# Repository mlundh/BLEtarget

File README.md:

# BLEtarget 
BLEtarget is an optical electronic scoring target with bluetooth connectivity developed for air guns. 

The project consists of both Hardware and firmware. The source is found in hw and fw respectively. 

## HW
The HW is developed in KiCad 7.0. It consists of a sensor array with support electronics as well as an STM32 with BLE capabilites. 

### Known bugs
BOM error - U8-U10 MCP604 populated with MCP6044 with 14kHz bandwidth, should be MCP604 with 2.8Mhz bandwidth.
BOM error - c32 and corresponding 10u caps should be changed to 10000PF for a shorter signal pulse.
Schematic error - add a jumper to select master/slave. 
Schematic update - add a small memory, fram.

## FW
The firmware developed in CubeIDE.

## SW
The user interface is called Bullseye and developed in Qt using widgets.

### Dependencies
qt6-base-dev-tools
qt6-serialport-dev
cmake

### Raspberry pi Zero 2W with Hyperpixel 4.0 Square
#### Increase swap file:
Edit /etc/dphys-swapfile to change CONF_SWAPSIZE=100 to CONF_SWAPSIZE=2048. After making the change, restart the Pi.
#### Enable Hyperpixel
Add one line in /boot/firmware/config.txt:
dtoverlay=vc4-kms-dpi-hyperpixel4sq
#### Convenience
Enable one-click open of files: 
In Accessories select File Manager
In File Manage select Preference.
Select "Open Files with One Click"
#### Add desktop shortcut
Add desktop shortcut by draging the application to the desktop. Also drag the updateBullseye.sh script to the desktop.

#### Start at bootup

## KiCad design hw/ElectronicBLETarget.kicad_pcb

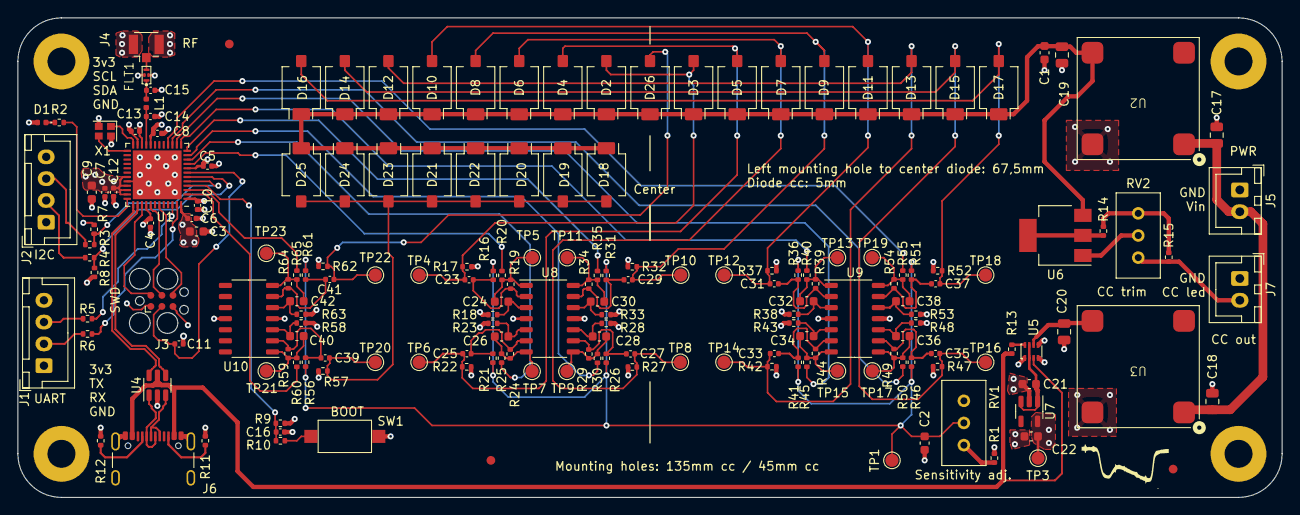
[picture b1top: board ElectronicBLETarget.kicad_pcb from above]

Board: 4 copper layers, 145.0 x 55.0 mm, 185 parts (0 on the bottom side), 91 nets.

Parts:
C1, C2, C3, C9, C21, C22: 4u7; C_0603_1608Metric
C4, C5, C6, C7, C8, C10, C11, C12, C13, C16, C23, C25, C27, C29, C31, C33, C35, C37, C39, C41: 100n; C_0402_1005Metric
C14: 0p8; C_0402_1005Metric
C15: 0p3; C_0402_1005Metric
C17, C18: 10u; C_0805_2012Metric
C19, C20: 22u; C_0805_2012Metric
C24, C26, C28, C30, C32, C34, C36, C38, C40, C42: 10u; C_0603_1608Metric
D1: LED; LED_0402_1005Metric
D2, D3, D4, D5, D6, D7, D8, D9, D10, D11, D12, D13, D14, D15, D16, D17, D18, D19, D20, D21, D22, D23, D24, D25, D26: BPW34-SMD; Osram_BPW34S-SMD
FLT1: DLF162500LT-5028A1
FM1, FM2, FM3: Fiducial; Fiducial_1mm_Mask2mm
H1, H2, H3, H4: MountingHole_Pad; MountingHole_3.2mm_M3_Pad
J1, J2: Conn_01x04; JST_XH_B4B-XH-A_1x04_P2.50mm_Vertical
J3: Conn_ARM_SWD_TagConnect_TC2030; Tag-Connect_TC2030-IDC-FP_2x03_P1.27mm_Vertical
J4: Conn_Coaxial; U.FL_Hirose_U.FL-R-SMT-1_Vertical
J5, J7: Conn_01x02; JST_XH_B2B-XH-A_1x02_P2.50mm_Vertical
J6: USB_C_Receptacle_USB2.0; USB_C_Receptacle_GCT_USB4105-xx-A_16P_TopMnt_Horizontal
L1: 2n7; L_0402_1005Metric
R1: 20k; R_0402_1005Metric
R2, R3, R4, R5, R6, R10, R20, R25, R30, R35, R40, R45, R50, R55, R60, R65: 220R; R_0402_1005Metric
R7, R8, R13, R17, R22, R27, R32, R37, R42, R47, R52, R57, R62: 5.6k; R_0402_1005Metric
R9, R11, R12: 5k1; R_0402_1005Metric
R14: 10R; R_0402_1005Metric
R15: 22R; R_0402_1005Metric
R16, R21, R26, R31, R36, R41, R46, R51, R56, R61: 100K; R_0402_1005Metric
R18, R23, R28, R33, R38, R43, R48, R53, R58, R63: 150K; R_0402_1005Metric
R19, R24, R29, R34, R39, R44, R49, R54, R59, R64: 1M; R_0402_1005Metric
RV1, RV2: 3296W; Potentiometer_Bourns_3296W_Vertical
SW1: SW_Push; SW_SPST_CK_RS282G05A3
TP1, TP3, TP4, TP5, TP6, TP7, TP8, TP9, TP10, TP11, TP12, TP13, TP14, TP15, TP16, TP17, TP18, TP19, TP20, TP21, TP22, TP23: TestPoint; TestPoint_Pad_D1.5mm
U1: STM32WB55CEU6; QFN-48-1EP_7x7mm_P0.5mm_EP5.6x5.6mm
U2: PXO7809-500-M-TR; PXO7805-500-M-TR
U3: PXO7805-500-M-TR
U4: USBLC6-2SC6; SOT-23-6
U5: LM66200; SOT-583-8
U6: LM317_SOT-223; SOT-223-3_TabPin2
U7: MIC5365-3.3YD5; SOT-23-5
U8, U9, U10: MCP604; SOIC-14_3.9x8.7mm_P1.27mm
X1: 32MHz, NX2016SA-32M; Crystal_SMD_2016-4Pin_2.0x1.6mm

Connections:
+3V3: C3.1, C4.1, C5.1, C6.1, C7.1, C8.1, C9.1, C10.1, C12.1, C13.1, C22.1, D1.2 (A), J1.4, J2.4, J3.1 (VCC), R1.1, R7.1, R8.1, SW1.2, TP3.1, U1.1 (VBAT), U1.8 (VDDA), U1.20 (VDD), U1.23 (VDDRF), U1.31 (VFBSMPS), U1.33 (VLXSMPS), U1.34 (VDDSMPS), U1.35 (VDD), U1.40 (VDDUSB), U1.48 (VDD), U7.5 (VOUT), U8.4 (V+), U9.4 (V+), U10.4 (V+)
+5V: C21.1, U5.2 (VOUT), U5.7 (VOUT), U7.1 (VIN), U7.3 (EN)
+9V: C1.1, C19.1, D2.1 (K), D3.1 (K), D4.1 (K), D5.1 (K), D6.1 (K), D7.1 (K), D8.1 (K), D9.1 (K), D10.1 (K), D11.1 (K), D12.1 (K), D13.1 (K), D14.1 (K), D15.1 (K), D16.1 (K), D17.1 (K), D18.1 (K), D19.1 (K), D20.1 (K), D21.1 (K), D22.1 (K), D23.1 (K), D24.1 (K), D25.1 (K), D26.1 (K), U2.3 (+Vout), U6.3 (VI)
+BATT: C17.1, C18.1, J5.2, U2.1 (+Vin), U3.1 (+Vin)
/BOOT0: C16.1, R9.1, R10.1, U1.4 (PH3)
/HSE_IN: U1.25 (OSC_IN), X1.3
/HSE_OUT: U1.24 (OSC_OUT), X1.1
/I2C_SCL: R3.2, R7.2, U1.5 (PB8)
/I2C_SCLC: J2.3, R3.1
/I2C_SDA: R4.2, R8.2, U1.6 (PB9)
/I2C_SDAC: J2.2, R4.1
/LED: R2.2, U1.36 (PA10)
/Power/USB_CC1: J6.A5 (CC1), R12.1
/Power/USB_CC2: J6.B5 (CC2), R11.1
/Power/USB_FD+: J6.A6 (D+), J6.B6 (D+), U4.3 (I/O2)
/Power/USB_FD-: J6.A7 (D-), J6.B7 (D-), U4.1 (I/O1)
/RF: C14.1, L1.1, U1.21 (RF1)
/RF_ANT: FLT1.3 (OUT), J4.1 (In)
/RF_MATCH: C15.1, FLT1.1 (IN), L1.2
/SWD_CLK: J3.4 (SWCLK), U1.41 (PA14)
/SWD_DIO: J3.2 (SWDIO), U1.39 (PA13)
/SWD_NRST: C11.1, J3.3 (~RESET), U1.7 (NRST)
/SWD_TRC: J3.6 (SWO), U1.43 (PB3)
/SensorArrayGroup1/SensorChannel1/ch1_Minus: C23.2, R16.2, R19.1, U8.2 (-)
/SensorArrayGroup1/SensorChannel1/ch1_Output: C24.2, R19.2, R20.2, TP5.1, U8.1
/SensorArrayGroup1/SensorChannel1/ch1_Positive: C24.1, R18.2, U8.3 (+)
/SensorArrayGroup1/SensorChannel1/ch1_d: C23.1, D2.2 (A), D3.2 (A), R17.1, TP4.1
/SensorArrayGroup1/SensorChannel2/ch2_Minus: C25.2, R21.2, R24.1, U8.6 (-)
/SensorArrayGroup1/SensorChannel2/ch2_Positive: C26.1, R23.2, U8.5 (+)
/SensorArrayGroup1/SensorChannel2/ch2_d: C25.1, D4.2 (A), D5.2 (A), R22.1, TP6.1
/SensorArrayGroup1/SensorChannel2/ch2_output: C26.2, R24.2, R25.2, TP7.1, U8.7
/SensorArrayGroup1/SensorChannel3/ch3_D: C27.1, D6.2 (A), D7.2 (A), R27.1, TP8.1
/SensorArrayGroup1/SensorChannel3/ch3_Minus: C27.2, R26.2, R29.1, U8.9 (-)
/SensorArrayGroup1/SensorChannel3/ch3_output: C28.2, R29.2, R30.2, TP9.1, U8.8
/SensorArrayGroup1/SensorChannel3/ch3_positive: C28.1, R28.2, U8.10 (+)
/SensorArrayGroup1/SensorChannel4/ch4_D: C29.1, D8.2 (A), D9.2 (A), R32.1, TP10.1
/SensorArrayGroup1/SensorChannel4/ch4_negative: C29.2, R31.2, R34.1, U8.13 (-)
/SensorArrayGroup1/SensorChannel4/ch4_output: C30.2, R34.2, R35.2, TP11.1, U8.14
/SensorArrayGroup1/SensorChannel4/ch4_positive: C30.1, R33.2, U8.12 (+)
/SensorArrayGroup1/TrimPotCenterTap: C2.1, R16.1, R21.1, R26.1, R31.1, R36.1, R41.1, R46.1, R51.1, R56.1, R61.1, RV1.2, TP1.1
/SensorArrayGroup2/SensorChannel5/ch1_Minus: C31.2, R36.2, R39.1, U9.2 (-)
/SensorArrayGroup2/SensorChannel5/ch1_Output: C32.2, R39.2, R40.2, TP13.1, U9.1
/SensorArrayGroup2/SensorChannel5/ch1_Positive: C32.1, R38.2, U9.3 (+)
/SensorArrayGroup2/SensorChannel5/ch1_d: C31.1, D10.2 (A), D11.2 (A), R37.1, TP12.1
/SensorArrayGroup2/SensorChannel6/ch2_Minus: C33.2, R41.2, R44.1, U9.6 (-)
/SensorArrayGroup2/SensorChannel6/ch2_Positive: C34.1, R43.2, U9.5 (+)
/SensorArrayGroup2/SensorChannel6/ch2_d: C33.1, D12.2 (A), D13.2 (A), R42.1, TP14.1
/SensorArrayGroup2/SensorChannel6/ch2_output: C34.2, R44.2, R45.2, TP15.1, U9.7
/SensorArrayGroup2/SensorChannel7/ch3_D: C35.1, D14.2 (A), D15.2 (A), R47.1, TP16.1
/SensorArrayGroup2/SensorChannel7/ch3_Minus: C35.2, R46.2, R49.1, U9.9 (-)
/SensorArrayGroup2/SensorChannel7/ch3_output: C36.2, R49.2, R50.2, TP17.1, U9.8
/SensorArrayGroup2/SensorChannel7/ch3_positive: C36.1, R48.2, U9.10 (+)
/SensorArrayGroup2/SensorChannel8/ch4_D: C37.1, D16.2 (A), D17.2 (A), R52.1, TP18.1
/SensorArrayGroup2/SensorChannel8/ch4_negative: C37.2, R51.2, R54.1, U9.13 (-)
/SensorArrayGroup2/SensorChannel8/ch4_output: C38.2, R54.2, R55.2, TP19.1, U9.14
/SensorArrayGroup2/SensorChannel8/ch4_positive: C38.1, R53.2, U9.12 (+)
/SensorArrayGroup3/SensorBackRow/back_d: C39.1, D18.2 (A), D19.2 (A), D20.2 (A), D21.2 (A), D22.2 (A), D23.2 (A), D24.2 (A), D25.2 (A), R57.1, TP20.1
/SensorArrayGroup3/SensorBackRow/back_minus: C39.2, R56.2, R59.1, U10.2 (-)
/SensorArrayGroup3/SensorBackRow/back_output: C40.2, R59.2, R60.2, TP21.1, U10.1
/SensorArrayGroup3/SensorBackRow/back_positive: C40.1, R58.2, U10.3 (+)
/SensorArrayGroup3/SensorCenter/center_Minus: C41.2, R61.2, R64.1, U10.6 (-)
/SensorArrayGroup3/SensorCenter/center_d: C41.1, D26.2 (A), R62.1, TP22.1
/SensorArrayGroup3/SensorCenter/center_output: C42.2, R64.2, R65.2, TP23.1, U10.7
/SensorArrayGroup3/SensorCenter/center_positive: C42.1, R63.2, U10.5 (+)
/USART1_RX: R6.2, U1.47 (PB7)
/USART1_RXC: J1.2, R6.1
/USART1_TX: R5.2, U1.46 (PB6)
/USART1_TXC: J1.3, R5.1
/USB_D+: U1.38 (PA12), U4.4 (I/O2)
/USB_D-: U1.37 (PA11), U4.6 (I/O1)
/ch1: R20.1, U1.9 (PA0)
/ch2: R25.1, U1.10 (PA1)
/ch3: R30.1, U1.11 (PA2)
/ch4: R35.1, U1.12 (PA3)
/ch5: R40.1, U1.13 (PA4)
/ch6: R45.1, U1.14 (PA5)
/ch7: R50.1, U1.15 (PA6)
/ch8: R55.1, U1.16 (PA7)
/chCenter: R65.1, U1.3 (PC15)
/chSide: R60.1, U1.2 (PC14)
GND: C1.2, C2.2, C3.2, C4.2, C5.2, C6.2, C7.2, C8.2, C9.2, C10.2, C11.2, C12.2, C13.2, C14.2, C15.2, C16.2, C17.2, C18.2, C19.2, C20.2, C21.2, C22.2, FLT1.2 (GND), FLT1.4 (GND), H1.1, H2.1, H3.1, H4.1, J1.1, J2.1, J3.5 (GND), J4.2 (Ext), J5.1, J6.A1 (GND), J6.A12 (GND), J6.B1 (GND), J6.B12 (GND), J6.S1 (SHIELD), J7.1, R9.2, R11.2, R12.2, R17.2, R18.1, R22.2, R23.1, R27.2, R28.1, R32.2, R33.1, R37.2, R38.1, R42.2, R43.1, R47.2, R48.1, R52.2, R53.1, R57.2, R58.1, R62.2, R63.1, RV1.3, U1.22 (VSSRF), U1.32 (VSSSMPS), U1.49 (VSS), U2.4 (GND), U3.4 (GND), U4.2 (GND), U5.1 (GND), U5.4 (ON_), U5.5 (GND), U7.2 (GND), U8.11 (V-), U9.11 (V-), U10.11 (V-), X1.2, X1.4
unnamed: D1.1 (K), R2.1
unnamed: J7.2, R15.2, RV2.1
unnamed: R1.2, RV1.1
unnamed: R10.2, SW1.1
unnamed: R14.2, R15.1, RV2.3
unnamed: C20.1, U3.3 (+Vout), U5.6 (VIN2)
unnamed: J6.A4 (VBUS), J6.A9 (VBUS), J6.B4 (VBUS), J6.B9 (VBUS), R13.1, U4.5 (VBUS), U5.3 (VIN1)
unnamed: R13.2, U5.8 (ST)
unnamed: RV2.2, U6.1 (ADJ)
unnamed: R14.1, U6.2 (VO)

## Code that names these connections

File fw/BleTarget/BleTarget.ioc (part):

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Mcu.Name=STM32WB55CEUx
Mcu.Package=UFQFPN48
Mcu.UserName=STM32WB55CEUx
PA0.GPIOParameters=GPIO_Label
PA0.GPIO_Label=CH_1
PA0.Signal=GPXTI0
PA1.GPIOParameters=GPIO_Label
PA1.GPIO_Label=CH_2
PA1.Signal=GPXTI1
PA10.GPIOParameters=GPIO_Speed,PinState,GPIO_PuPd,GPIO_Label,GPIO_ModeDefaultOutputPP
PA10.GPIO_Label=LED
PA10.GPIO_ModeDefaultOutputPP=GPIO_MODE_OUTPUT_OD
PA10.GPIO_PuPd=GPIO_NOPULL
PA10.GPIO_Speed=GPIO_SPEED_FREQ_MEDIUM
PA10.PinState=GPIO_PIN_SET
PA10.Signal=GPIO_Output
PA11.Mode=Device
PA11.Signal=USB_DM
PA12.Mode=Device
PA12.Signal=USB_DP
PA13.Mode=Trace_Asynchronous_SW
PA13.Signal=SYS_JTMS-SWDIO
PA14.Mode=Trace_Asynchronous_SW
PA14.Signal=SYS_JTCK-SWCLK
PA2.GPIOParameters=GPIO_Label
PA2.GPIO_Label=CH_3
PA2.Signal=GPXTI2
PA3.GPIOParameters=GPIO_Label
PA3.GPIO_Label=CH_4
PA3.Signal=GPXTI3
PA4.GPIOParameters=GPIO_Label
PA4.GPIO_Label=CH_5
PA4.Signal=GPXTI4
PA5.GPIOParameters=GPIO_Label
PA5.GPIO_Label=CH_6
PA5.Signal=GPXTI5
PA6.GPIOParameters=GPIO_Label
PA6.GPIO_Label=CH_7
PA6.Signal=GPXTI6
PA7.GPIOParameters=GPIO_Label
PA7.GPIO_Label=CH_8
PA7.Signal=GPXTI7
PB3.Mode=Trace_Asynchronous_SW
PB3.Signal=SYS_JTDO-SWO
PB6.Mode=Asynchronous
PB6.Signal=USART1_TX
PB7.Mode=Asynchronous
PB7.Signal=USART1_RX
PB8.Mode=I2C
PB8.Signal=I2C1_SCL
PB9.Mode=I2C
PB9.Signal=I2C1_SDA
PC14-OSC32_IN.GPIOParameters=GPIO_Label
PC14-OSC32_IN.GPIO_Label=CH_B
PC14-OSC32_IN.Signal=GPXTI14
PC15-OSC32_OUT.GPIOParameters=GPIO_Label
PC15-OSC32_OUT.GPIO_Label=CH_C
PC15-OSC32_OUT.Signal=GPXTI15
PH3-BOOT0.GPIOParameters=GPIO_Label
PH3-BOOT0.GPIO_Label=BOOT
PH3-BOOT0.Signal=GPIO_Input
RCC.HSE_VALUE=32000000
RCC.SYSCLKFreq_VALUE=64000000
RCC.SYSCLKSource=RCC_SYSCLKSOURCE_PLLCLK
board=custom

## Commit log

2024-05-06 HW as sent for manufacturing at PCBway.
2024-05-06 Fix: gitignore did not ignore all temp files.
2024-07-14 Initial firmware push. Sensor detects rising edges and computes position and velocity.
2024-07-24 Update gitignore to ignore metadatafiles from eclipse and backups from kicad.
2024-07-26 QT application talks to BLE target via UART.
2024-07-26 remove untracked files
2024-07-26 Update gitignore
2024-07-26 Update readme file with bugs.
2024-07-27 Feature: Two cards communicate over i2c, and the master transmitts the complete data to the SW application.
2024-08-02 Add heartbeat function and show speed of last pellet.
2024-08-02 Clear speed on button.
2024-08-03 fix: add new speed measurements.
2024-08-04 Start application in fullscreen. Create a simple script to pull the repo and rebuild as a means for easy updates.
2024-08-04 Add .desctop files.
2024-08-04 Update .desktop files.
2024-08-04 Update icon and fix desctop files for target.
2024-08-04 Might work now.
2024-08-15 Send both speed measues (x and Y) to Bullseye. Show both of these on the GUI.
    Add button to save scores to file. Naive first solution, saves all registered hits since the program was started.
2024-08-16 clear both x and y speed
